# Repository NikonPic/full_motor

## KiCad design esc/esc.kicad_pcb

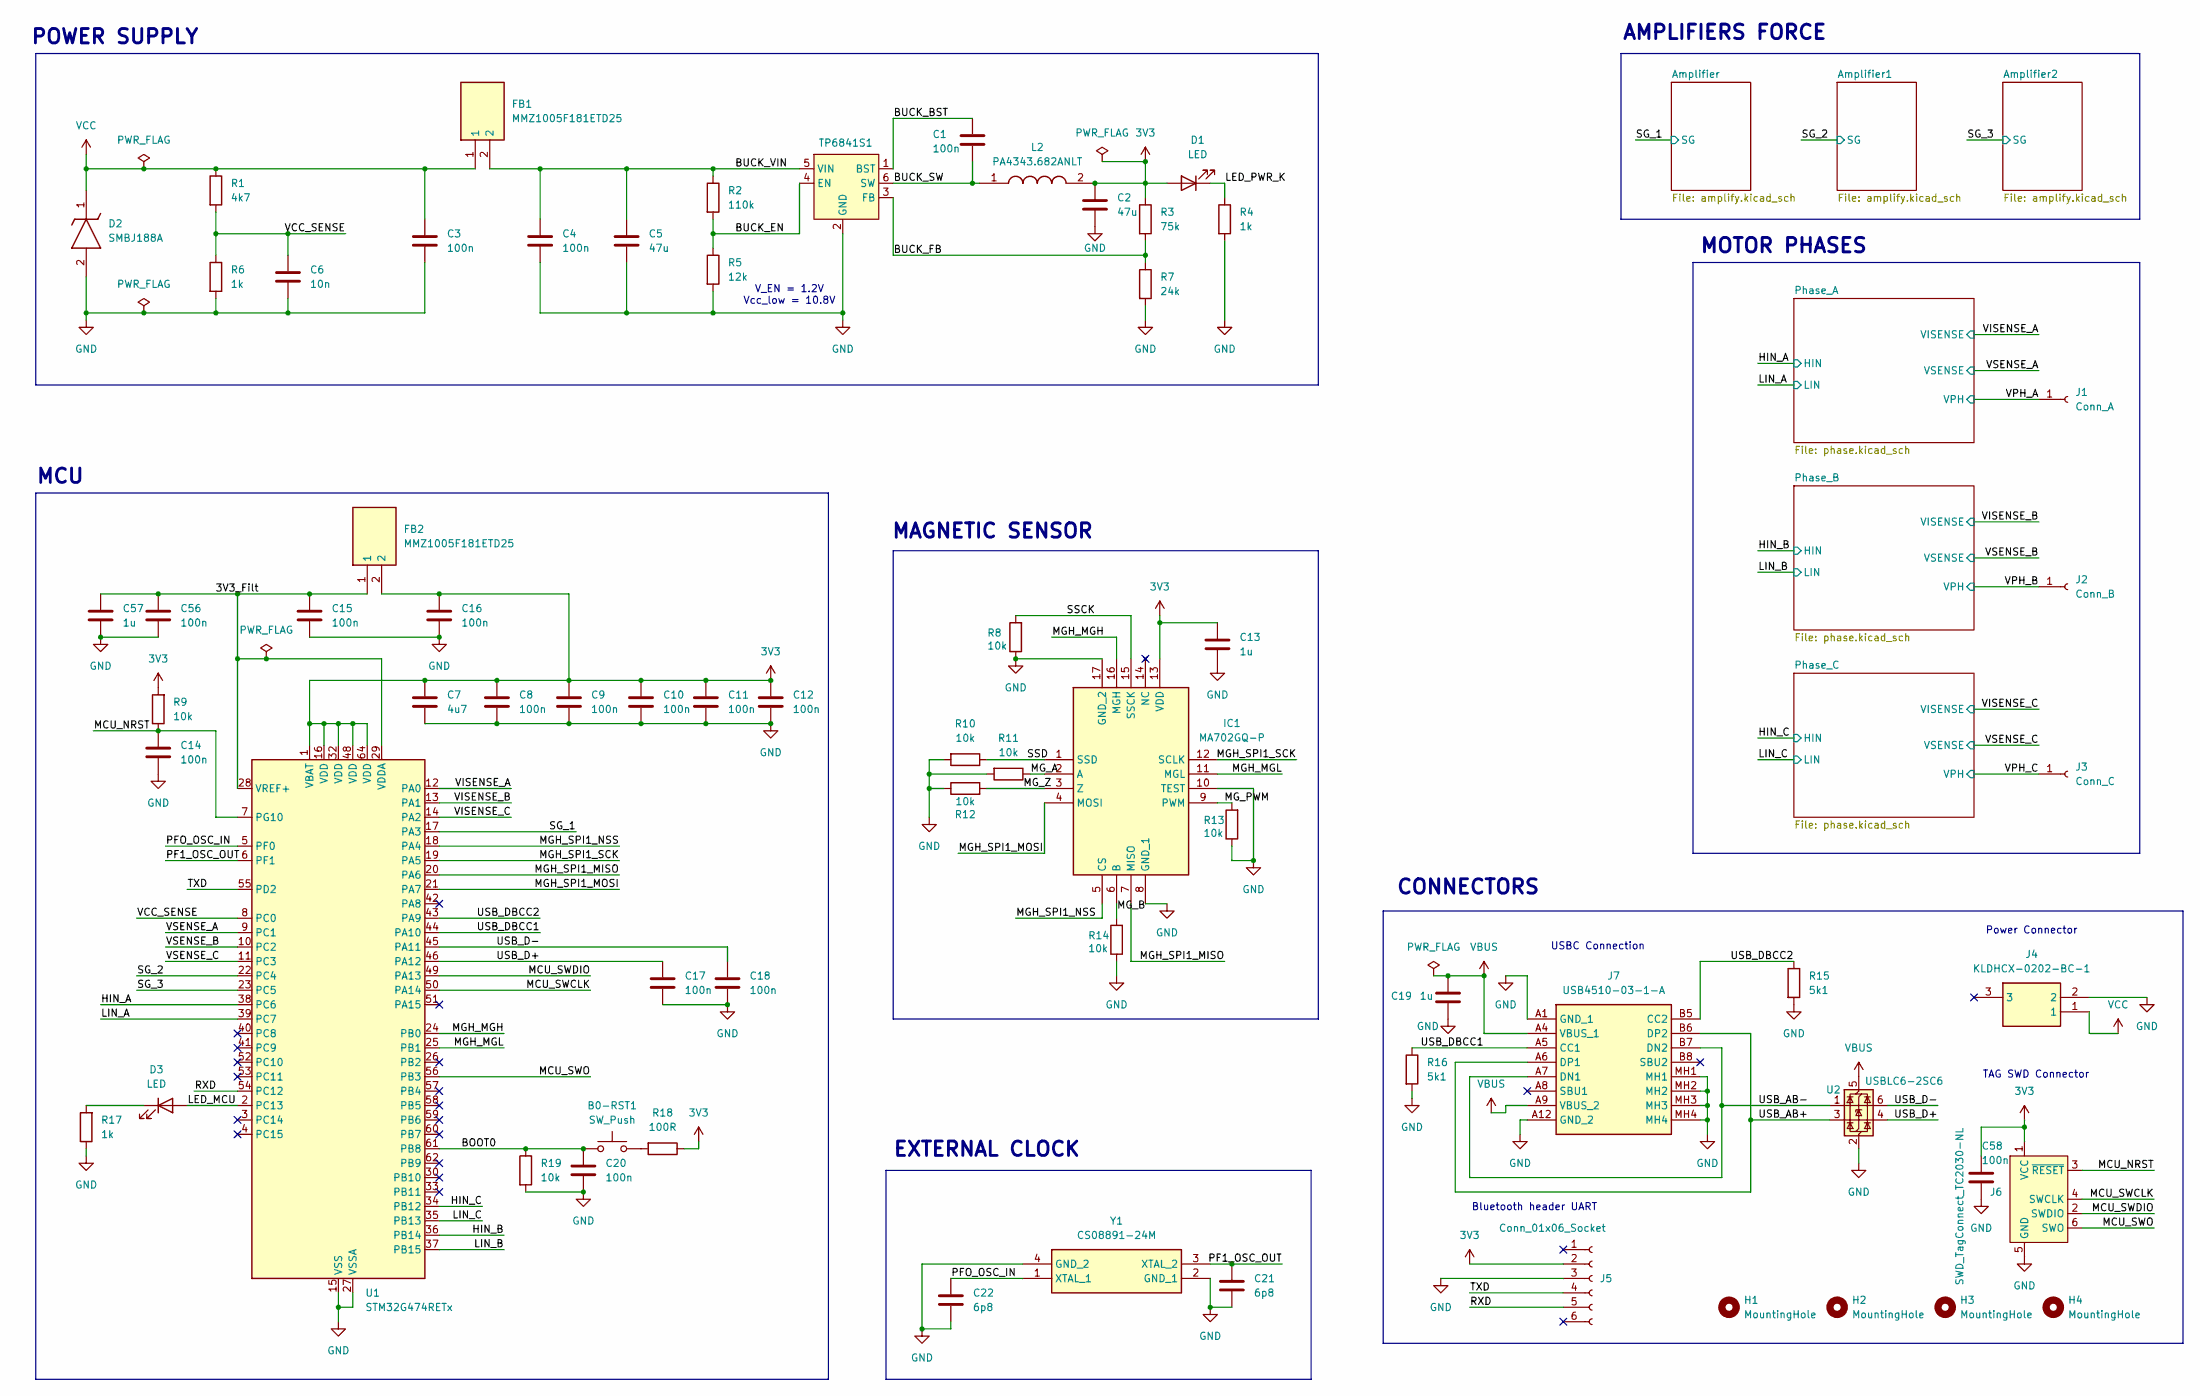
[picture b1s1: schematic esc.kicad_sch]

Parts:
B0-RST1: SW_Push; SW_SPST_B3U-1000P; MPN 653-B3U-1000P
C1, C3, C4, C8, C9, C10, C11, C12, C14, C15, C16, C17, C18, C20, C56, C58: 100n; C_0402_1005Metric; MPN 81-GRM02YR60G104ME1L
C2, C5: 47u; C_1206_3216Metric; Manufacturer_Part_Number MLASE31LBB5476MTNA01; Mouser Part Number 963-MLASE31LBB5476MT
C6: 10n; C_0402_1005Metric; MPN 77-V0402Y103KXJAC31X
C7: 4u7; C_0603_1608Metric; MPN 963-MLASE168AB5475KT
C13, C19, C57: 1u; C_0603_1608Metric; MPN 963-BJCT168CB7105KR
C21, C22: 6p8; C_0402_1005Metric; MPN 81-GJM0225C1C6R8CB1L
D1, D3: LED; LED_0603_1608Metric; MPN 720-GWJTLMS3.G3G758
D2: SMBJ188A; DIOM5436X244N; Manufacturer_Part_Number SMBJ18A
FB1, FB2: MMZ1005F181ETD25; BEADC1005X55N; Manufacturer_Part_Number MMZ1005F181ETD25; Mouser Part Number 810-MMZ1005F181ETD25
H1, H2, H3, H4: MountingHole; MountingHole_3.2mm_M3
IC1: MA702GQ-P; QFN50P300X300X100-17N-D; Manufacturer_Part_Number MA702GQ-P; Mouser Part Number 946-MA702GQ-P
J1: Conn_A; SolderWire-2sqmm_1x01_D2mm_OD3.9mm
J2: Conn_B; SolderWire-2sqmm_1x01_D2mm_OD3.9mm
J3: Conn_C; SolderWire-2sqmm_1x01_D2mm_OD3.9mm
J4: KLDHCX-0202-BC-1; KLDHCX0202BC1; Manufacturer_Part_Number KLDHCX-0202-BC-1; Mouser Part Number 806-KLDHCX-0202-BC-1
J5: Conn_01x06_Socket; PinSocket_1x06_P2.54mm_Vertical; MPN 437-3158710641003101
J6: SWD_TagConnect_TC2030-NL; Tag-Connect_TC2030-IDC-NL_2x03_P1.27mm_Vertical
J7: USB4510-03-1-A; USB4510031A; Manufacturer_Part_Number USB4510-03-1-A; Mouser Part Number 640-USB4510031A
L2: PA4343.682ANLT; INDPM135126X650N; Manufacturer_Part_Number PA4343.682ANLT; Mouser Part Number 673-PA4343.682ANLT
R1: 4k7; R_0603_1608Metric; MPN 754-RG1608N-472-WT5
R2: 110k; R_0603_1608Metric; MPN 594-MCT06030C1103FP5
R3: 75k; R_0603_1608Metric; MPN 603-RT0603FRE1375KL
R4, R6, R17: 1k; R_0603_1608Metric; MPN 71-CRCW06031K00FKED
R5: 12k; R_0603_1608Metric; MPN 594-MCS04020D1202BE0
R7: 24k; R_0603_1608Metric; MPN 667-ERA-3AEB243V
R8, R9, R10, R11, R12, R13, R14, R19: 10k; R_0603_1608Metric; MPN 708-RNCE0603BTE10K0
R15, R16: 5k1; R_0603_1608Metric; MPN 594-MCT06030C5101FPW
R18: 100R; R_0603_1608Metric; MPN 708-RNCE0603BTE100R
TP6841S1: SOT-23-6
U1: STM32G474RETx; LQFP-64_10x10mm_P0.5mm; MPN 511-STM32G474RET6
U2: USBLC6-2SC6; SOT-23-6; Manufacturer_Part_Number USBLC6-2SC6; Mouser Part Number 511-USBLC6-2SC6
Y1: CS08891-24M; NX2016SA24MEXS00ACS08891; Manufacturer_Part_Number NX2016SA-24M-EXS00A-CS08891; Mouser Part Number 344-NX2016SA24S08891

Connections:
3V3: C2.1, C7.1, C8.1, C9.1, C10.1, C11.1, C12.1, C13.1, C16.1, C58.1, D1.2 (A), FB2.2, IC1.13 (VDD), J5.2, J6.1 (VCC), L2.2, R3.1, R9.2, R18.1, U1.1 (VBAT), U1.16 (VDD), U1.32 (VDD), U1.48 (VDD), U1.64 (VDD); also elsewhere on the board
/3V3_Filt: C15.1, C56.1, C57.1, FB2.1, U1.28 (VREF+), U1.29 (VDDA)
/BOOT0: B0-RST1.1, C20.1, R19.1, U1.61 (PB8)
/BUCK_BST: C1.1, TP6841S1.1 (BST)
/BUCK_EN: R2.2, R5.1, TP6841S1.4 (EN)
/BUCK_FB: R3.2, R7.1, TP6841S1.3 (FB)
/BUCK_SW: C1.2, L2.1, TP6841S1.6 (SW)
/BUCK_VIN: C4.1, C5.1, FB1.2, R2.1, TP6841S1.5 (VIN)
/HIN_A: U1.38 (PC6); also elsewhere on the board
/HIN_B: U1.36 (PB14); also elsewhere on the board
/HIN_C: U1.34 (PB12); also elsewhere on the board
/LED_MCU: D3.2 (A), U1.2 (PC13)
/LED_PWR_K: D1.1 (K), R4.1
/LIN_A: U1.39 (PC7); also elsewhere on the board
/LIN_B: U1.37 (PB15); also elsewhere on the board
/LIN_C: U1.35 (PB13); also elsewhere on the board
/MCU_NRST: C14.1, J6.3 (~RESET), R9.1, U1.7 (PG10)
/MCU_SWCLK: J6.4 (SWCLK), U1.50 (PA14)
/MCU_SWDIO: J6.2 (SWDIO), U1.49 (PA13)
/MCU_SWO: J6.6 (SWO), U1.56 (PB3)
/MGH_MGH: IC1.16 (MGH), U1.24 (PB0)
/MGH_MGL: IC1.11 (MGL), U1.25 (PB1)
/MGH_SPI1_MISO: IC1.7 (MISO), U1.20 (PA6)
/MGH_SPI1_MOSI: IC1.4 (MOSI), U1.21 (PA7)
/MGH_SPI1_NSS: IC1.5 (CS), U1.18 (PA4)
/MGH_SPI1_SCK: IC1.12 (SCLK), U1.19 (PA5)
/MG_A: IC1.2 (A), R11.1
/MG_B: IC1.6 (B), R14.2
/MG_PWM: IC1.9 (PWM), R13.2
/MG_Z: IC1.3 (Z), R12.2
/PF1_OSC_OUT: C21.1, U1.6 (PF1), Y1.3 (XTAL_2)
/PFO_OSC_IN: C22.1, U1.5 (PF0), Y1.1 (XTAL_1)
/RXD: J5.5, U1.54 (PC12)
/SG_1: U1.17 (PA3); also elsewhere on the board
/SG_2: U1.22 (PC4); also elsewhere on the board
/SG_3: U1.23 (PC5); also elsewhere on the board
/SSCK: IC1.15 (SSCK), R8.2
/SSD: IC1.1 (SSD), R10.1
/TXD: J5.4, U1.55 (PD2)
/USB_AB+: J7.A6 (DP1), J7.B6 (DP2), U2.3 (I/O2)
/USB_AB-: J7.A7 (DN1), J7.B7 (DN2), U2.1 (I/O1)
/USB_D+: C17.1, U1.46 (PA12), U2.4 (I/O2)
/USB_D-: C18.1, U1.45 (PA11), U2.6 (I/O1)
/USB_DBCC1: J7.A5 (CC1), R16.1, U1.44 (PA10)
/USB_DBCC2: J7.B5 (CC2), R15.1, U1.43 (PA9)
/VCC_SENSE: C6.1, R1.2, R6.1, U1.8 (PC0)
/VISENSE_A: U1.12 (PA0); also elsewhere on the board
/VISENSE_B: U1.13 (PA1); also elsewhere on the board
/VISENSE_C: U1.14 (PA2); also elsewhere on the board
/VPH_A: J1.1; also elsewhere on the board
/VPH_B: J2.1; also elsewhere on the board
/VPH_C: J3.1; also elsewhere on the board
/VSENSE_A: U1.9 (PC1); also elsewhere on the board
/VSENSE_B: U1.10 (PC2); also elsewhere on the board
/VSENSE_C: U1.11 (PC3); also elsewhere on the board
GND: C2.2, C3.2, C4.2, C5.2, C6.2, C7.2, C8.2, C9.2, C10.2, C11.2, C12.2, C13.2, C14.2, C15.2, C16.2, C17.2, C18.2, C19.2, C20.2, C21.2, C22.2, C56.2, C57.2, C58.2, D2.2 (A), IC1.8 (GND_1), IC1.10 (TEST), IC1.17 (GND_2), J4.2, J5.3, J6.5 (GND), J7.A1 (GND_1), J7.A12 (GND_2), J7.MH1, J7.MH2, J7.MH3, J7.MH4, R4.2, R5.2, R6.2, R7.2, R8.1, R10.2, R11.2, R12.1, R13.1, R14.1, R15.2, R16.2, R17.1, R19.2, TP6841S1.2 (GND), U1.15 (VSS), U1.27 (VSSA), U1.31 (VSS), U1.47 (VSS), U1.63 (VSS), U2.2 (GND), Y1.2 (GND_1), Y1.4 (GND_2); also elsewhere on the board
unnamed: B0-RST1.2, R18.2
unnamed: D3.1 (K), R17.2
VBUS: C19.1, J7.A4 (VBUS_1), J7.A9 (VBUS_2), U2.5 (VBUS)
VCC: C3.1, D2.1 (K), FB1.1, J4.1, R1.1; also elsewhere on the board

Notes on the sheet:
MOTOR PHASES
POWER SUPPLY
CONNECTORS
MCU
TAG SWD Connector
Power Connector
AMPLIFIERS FORCE
USBC Connection
MAGNETIC SENSOR
V_EN = 1.2V Vcc_low = 10.8V
EXTERNAL CLOCK
Bluetooth header UART

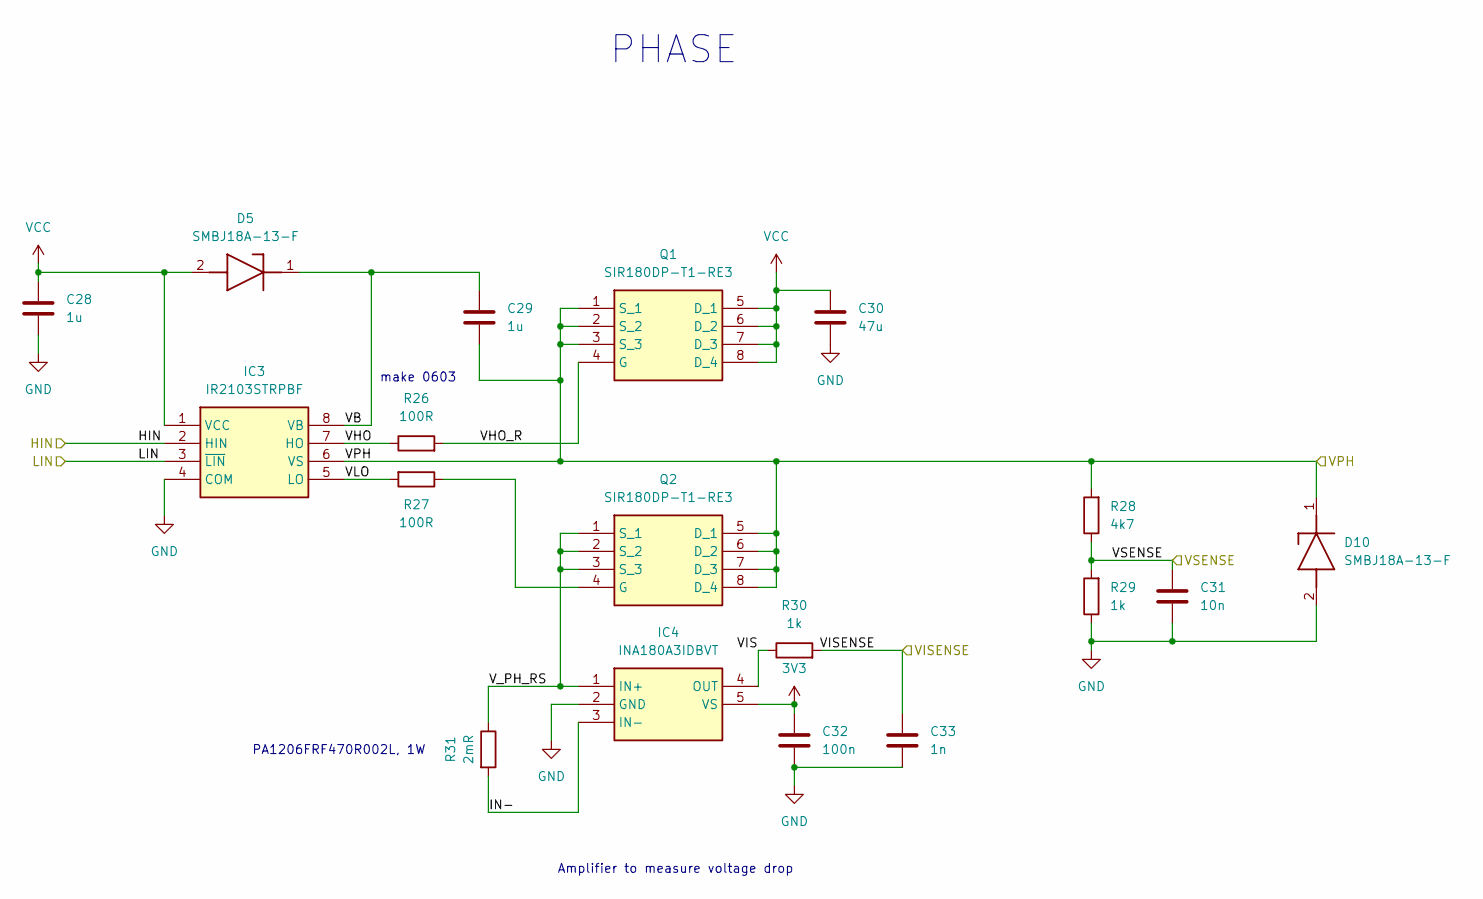
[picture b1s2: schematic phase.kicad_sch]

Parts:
C28, C29: 1u; C_0603_1608Metric; MPN 963-BJCT168CB7105KR
C30: 47u; C_1206_3216Metric; Manufacturer_Part_Number MLASE31LBB5476MTNA01; Mouser Part Number 963-MLASE31LBB5476MT
C31: 10n; C_0402_1005Metric; MPN 77-V0402Y103KXJAC31X
C32: 100n; C_0402_1005Metric; MPN 81-GRM02YR60G104ME1L
C33: 1n; C_0402_1005Metric; MPN 963-MLASE042SB5102MW
D5, D10: SMBJ18A-13-F; DIOM5336X250N; Manufacturer_Part_Number SMBJ18A-13-F; Mouser Part Number 621-SMBJ18A-13-F
IC3: IR2103STRPBF; SOIC127P600X175-8N; Manufacturer_Part_Number IR2103STRPBF; Mouser Part Number 942-IR2103STRPBF
IC4: INA180A3IDBVT; SOT95P280X145-5N; Manufacturer_Part_Number INA180A3IDBVT; Mouser Part Number 595-INA180A3IDBVT
Q1, Q2: SIR180DP-T1-RE3; SI7141DPT1GE3; Manufacturer_Part_Number SiR180DP-T1-RE3; Mouser Part Number 78-SIR180DP-T1-RE3
R26, R27: 100R; R_0603_1608Metric; MPN 708-RNCE0603BTE100R
R28: 4k7; R_0603_1608Metric; MPN 754-RG1608N-472-WT5
R29, R30: 1k; R_0603_1608Metric; MPN 71-CRCW06031K00FKED
R31: 2mR; R_1206_3216Metric; MPN 603-P1206FRF470R002L

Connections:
3V3: C32.1, IC4.5 (VS); also elsewhere on the board
/HIN_A: IC3.2 (HIN); also elsewhere on the board
/LIN_A: IC3.3 (~LIN); also elsewhere on the board
/Phase_A/IN-: IC4.3 (IN-), R31.2
/Phase_A/VB: C29.1, D5.1 (K), IC3.8 (VB)
/Phase_A/VHO: IC3.7 (HO), R26.1
/Phase_A/VHO_R: Q1.4 (G), R26.2
/Phase_A/VIS: IC4.4 (OUT), R30.1
/Phase_A/VLO: IC3.5 (LO), R27.2
/Phase_A/V_PH_RS: IC4.1 (IN+), Q2.1 (S_1), Q2.2 (S_2), Q2.3 (S_3), R31.1
/VISENSE_A: C33.1, R30.2; also elsewhere on the board
/VPH_A: C29.2, D10.1 (K), IC3.6 (VS), Q1.1 (S_1), Q1.2 (S_2), Q1.3 (S_3), Q2.5 (D_1), Q2.6 (D_2), Q2.7 (D_3), Q2.8 (D_4), R28.2; also elsewhere on the board
/VSENSE_A: C31.1, R28.1, R29.2; also elsewhere on the board
GND: C28.2, C30.2, C31.2, C32.2, C33.2, D10.2 (A), IC3.4 (COM), IC4.2 (GND), R29.1; also elsewhere on the board
unnamed: Q2.4 (G), R27.1
VCC: C28.1, C30.1, D5.2 (A), IC3.1 (VCC), Q1.5 (D_1), Q1.6 (D_2), Q1.7 (D_3), Q1.8 (D_4); also elsewhere on the board

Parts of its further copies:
C34, C35, C45, C46: 1u; C_0603_1608Metric; MPN 963-BJCT168CB7105KR
C36, C47: 47u; C_1206_3216Metric; Manufacturer_Part_Number MLASE31LBB5476MTNA01; Mouser Part Number 963-MLASE31LBB5476MT
C37, C48: 10n; C_0402_1005Metric; MPN 77-V0402Y103KXJAC31X
C38, C49: 100n; C_0402_1005Metric; MPN 81-GRM02YR60G104ME1L
C39, C50: 1n; C_0402_1005Metric; MPN 963-MLASE042SB5102MW
D7, D9, D11, D12: SMBJ18A-13-F; DIOM5336X250N; Manufacturer_Part_Number SMBJ18A-13-F; Mouser Part Number 621-SMBJ18A-13-F
IC5, IC8: IR2103STRPBF; SOIC127P600X175-8N; Manufacturer_Part_Number IR2103STRPBF; Mouser Part Number 942-IR2103STRPBF
IC6, IC9: INA180A3IDBVT; SOT95P280X145-5N; Manufacturer_Part_Number INA180A3IDBVT; Mouser Part Number 595-INA180A3IDBVT
Q3, Q4, Q5, Q6: SIR180DP-T1-RE3; SI7141DPT1GE3; Manufacturer_Part_Number SiR180DP-T1-RE3; Mouser Part Number 78-SIR180DP-T1-RE3
R32, R33, R44, R45: 100R; R_0603_1608Metric; MPN 708-RNCE0603BTE100R
R34, R46: 4k7; R_0603_1608Metric; MPN 754-RG1608N-472-WT5
R35, R36, R47, R48: 1k; R_0603_1608Metric; MPN 71-CRCW06031K00FKED
R37, R49: 2mR; R_1206_3216Metric; MPN 603-P1206FRF470R002L

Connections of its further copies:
3V3: C38.1, C49.1, IC6.5 (VS), IC9.5 (VS); also elsewhere on the board
/HIN_B: IC5.2 (HIN); also elsewhere on the board
/HIN_C: IC8.2 (HIN); also elsewhere on the board
/LIN_B: IC5.3 (~LIN); also elsewhere on the board
/LIN_C: IC8.3 (~LIN); also elsewhere on the board
/Phase_B/IN-: IC6.3 (IN-), R37.2
/Phase_B/VB: C35.1, D7.1 (K), IC5.8 (VB)
/Phase_B/VHO: IC5.7 (HO), R32.1
/Phase_B/VHO_R: Q3.4 (G), R32.2
/Phase_B/VIS: IC6.4 (OUT), R36.1
/Phase_B/VLO: IC5.5 (LO), R33.2
/Phase_B/V_PH_RS: IC6.1 (IN+), Q4.1 (S_1), Q4.2 (S_2), Q4.3 (S_3), R37.1
/Phase_C/IN-: IC9.3 (IN-), R49.2
/Phase_C/VB: C46.1, D9.1 (K), IC8.8 (VB)
/Phase_C/VHO: IC8.7 (HO), R44.1
/Phase_C/VHO_R: Q5.4 (G), R44.2
/Phase_C/VIS: IC9.4 (OUT), R48.1
/Phase_C/VLO: IC8.5 (LO), R45.2
/Phase_C/V_PH_RS: IC9.1 (IN+), Q6.1 (S_1), Q6.2 (S_2), Q6.3 (S_3), R49.1
/VISENSE_B: C39.1, R36.2; also elsewhere on the board
/VISENSE_C: C50.1, R48.2; also elsewhere on the board
/VPH_B: C35.2, D11.1 (K), IC5.6 (VS), Q3.1 (S_1), Q3.2 (S_2), Q3.3 (S_3), Q4.5 (D_1), Q4.6 (D_2), Q4.7 (D_3), Q4.8 (D_4), R34.2; also elsewhere on the board
/VPH_C: C46.2, D12.1 (K), IC8.6 (VS), Q5.1 (S_1), Q5.2 (S_2), Q5.3 (S_3), Q6.5 (D_1), Q6.6 (D_2), Q6.7 (D_3), Q6.8 (D_4), R46.2; also elsewhere on the board
/VSENSE_B: C37.1, R34.1, R35.2; also elsewhere on the board
/VSENSE_C: C48.1, R46.1, R47.2; also elsewhere on the board
GND: C34.2, C36.2, C37.2, C38.2, C39.2, C45.2, C47.2, C48.2, C49.2, C50.2, D11.2 (A), D12.2 (A), IC5.4 (COM), IC6.2 (GND), IC8.4 (COM), IC9.2 (GND), R35.1, R47.1; also elsewhere on the board
unnamed: Q4.4 (G), R33.1
unnamed: Q6.4 (G), R45.1
VCC: C34.1, C36.1, C45.1, C47.1, D7.2 (A), D9.2 (A), IC5.1 (VCC), IC8.1 (VCC), Q3.5 (D_1), Q3.6 (D_2), Q3.7 (D_3), Q3.8 (D_4), Q5.5 (D_1), Q5.6 (D_2), Q5.7 (D_3), Q5.8 (D_4); also elsewhere on the board

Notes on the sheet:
PA1206FRF470R002L, 1W
PHASE
make 0603
Amplifier to measure voltage drop

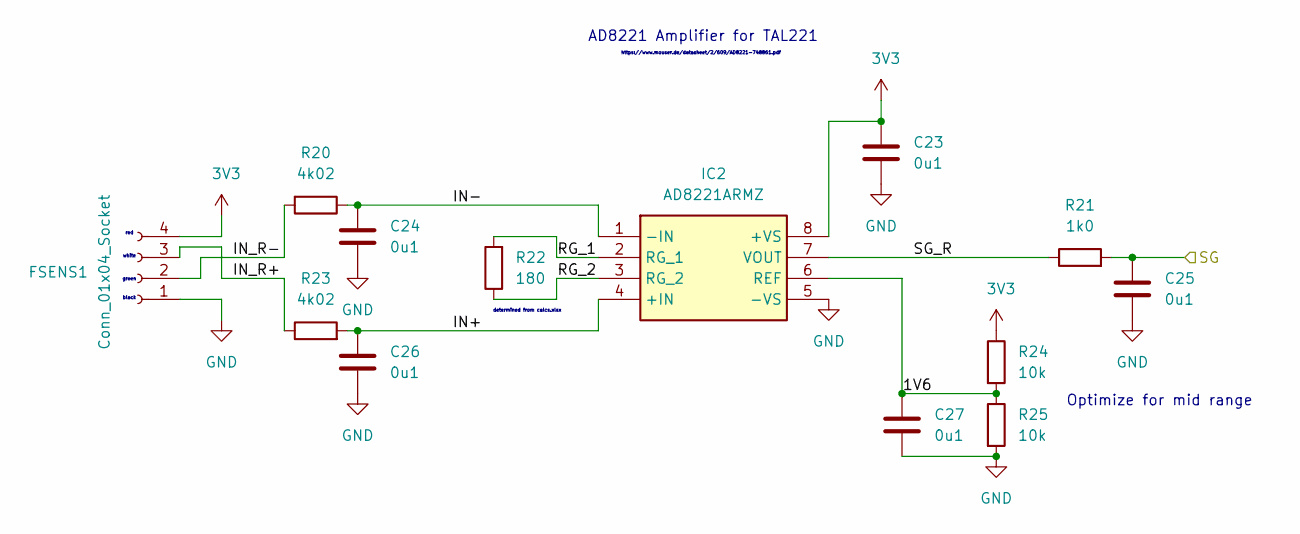
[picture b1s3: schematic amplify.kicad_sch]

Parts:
C23, C24, C25, C26, C27: 0u1; C_0603_1608Metric; MPN 187-CL10B104KB8NFNC
FSENS1: Conn_01x04_Socket; JST_XH_S4B-XH-A-1_1x04_P2.50mm_Horizontal; MPN 306-S4B-XH-ALFSN
IC2: AD8221ARMZ; SOP65P490X110-8N; Manufacturer_Part_Number AD8221ARMZ; Mouser Part Number 584-AD8221ARMZ
R20, R23: 4k02; R_0603_1608Metric; MPN 754-RR0816P-4021D59H
R21: 1k0; R_0603_1608Metric; MPN 71-CRCW06031K00FKED
R22: 180; R_0603_1608Metric; MPN 603-RT0603FRD07180RL
R24, R25: 10k; R_0603_1608Metric; MPN 708-RNCE0603BTE10K0

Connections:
3V3: C23.1, FSENS1.4, IC2.8 (+VS), R24.1; also elsewhere on the board
/Amplifier1/1V6: C27.1, IC2.6 (REF), R24.2, R25.1
/Amplifier1/IN+: C26.1, IC2.4 (+IN), R23.2
/Amplifier1/IN-: C24.1, IC2.1 (-IN), R20.1
/Amplifier1/IN_R+: FSENS1.3, R23.1
/Amplifier1/IN_R-: FSENS1.2, R20.2
/Amplifier1/RG_1: IC2.2 (RG_1), R22.2
/Amplifier1/RG_2: IC2.3 (RG_2), R22.1
/Amplifier1/SG_R: IC2.7 (VOUT), R21.1
/SG_2: C25.1, R21.2; also elsewhere on the board
GND: C23.2, C24.2, C25.2, C26.2, C27.2, FSENS1.1, IC2.5 (-VS), R25.2; also elsewhere on the board

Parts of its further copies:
C40, C41, C42, C43, C44, C51, C52, C53, C54, C55: 0u1; C_0603_1608Metric; MPN 187-CL10B104KB8NFNC
FSENS2, FSENS3: Conn_01x04_Socket; JST_XH_S4B-XH-A-1_1x04_P2.50mm_Horizontal; MPN 306-S4B-XH-ALFSN
IC7, IC10: AD8221ARMZ; SOP65P490X110-8N; Manufacturer_Part_Number AD8221ARMZ; Mouser Part Number 584-AD8221ARMZ
R38, R41, R50, R53: 4k02; R_0603_1608Metric; MPN 754-RR0816P-4021D59H
R39, R51: 1k0; R_0603_1608Metric; MPN 71-CRCW06031K00FKED
R40, R52: 180; R_0603_1608Metric; MPN 603-RT0603FRD07180RL
R42, R43, R54, R55: 10k; R_0603_1608Metric; MPN 708-RNCE0603BTE10K0

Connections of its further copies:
3V3: C40.1, C51.1, FSENS2.4, FSENS3.4, IC7.8 (+VS), IC10.8 (+VS), R42.1, R54.1; also elsewhere on the board
/Amplifier2/1V6: C55.1, IC10.6 (REF), R54.2, R55.1
/Amplifier2/IN+: C54.1, IC10.4 (+IN), R53.2
/Amplifier2/IN-: C52.1, IC10.1 (-IN), R50.1
/Amplifier2/IN_R+: FSENS3.3, R53.1
/Amplifier2/IN_R-: FSENS3.2, R50.2
/Amplifier2/RG_1: IC10.2 (RG_1), R52.2
/Amplifier2/RG_2: IC10.3 (RG_2), R52.1
/Amplifier2/SG_R: IC10.7 (VOUT), R51.1
/Amplifier/1V6: C44.1, IC7.6 (REF), R42.2, R43.1
/Amplifier/IN+: C43.1, IC7.4 (+IN), R41.2
/Amplifier/IN-: C41.1, IC7.1 (-IN), R38.1
/Amplifier/IN_R+: FSENS2.3, R41.1
/Amplifier/IN_R-: FSENS2.2, R38.2
/Amplifier/RG_1: IC7.2 (RG_1), R40.2
/Amplifier/RG_2: IC7.3 (RG_2), R40.1
/Amplifier/SG_R: IC7.7 (VOUT), R39.1
/SG_1: C42.1, R39.2; also elsewhere on the board
/SG_3: C53.1, R51.2; also elsewhere on the board
GND: C40.2, C41.2, C42.2, C43.2, C44.2, C51.2, C52.2, C53.2, C54.2, C55.2, FSENS2.1, FSENS3.1, IC7.5 (-VS), IC10.5 (-VS), R43.2, R55.2; also elsewhere on the board

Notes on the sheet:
Optimize for mid range
https://www.mouser.de/datasheet/2/609/AD8221-748861.pdf
red
green
white
AD8221 Amplifier for TAL221
black
determined from calcs.xlsx

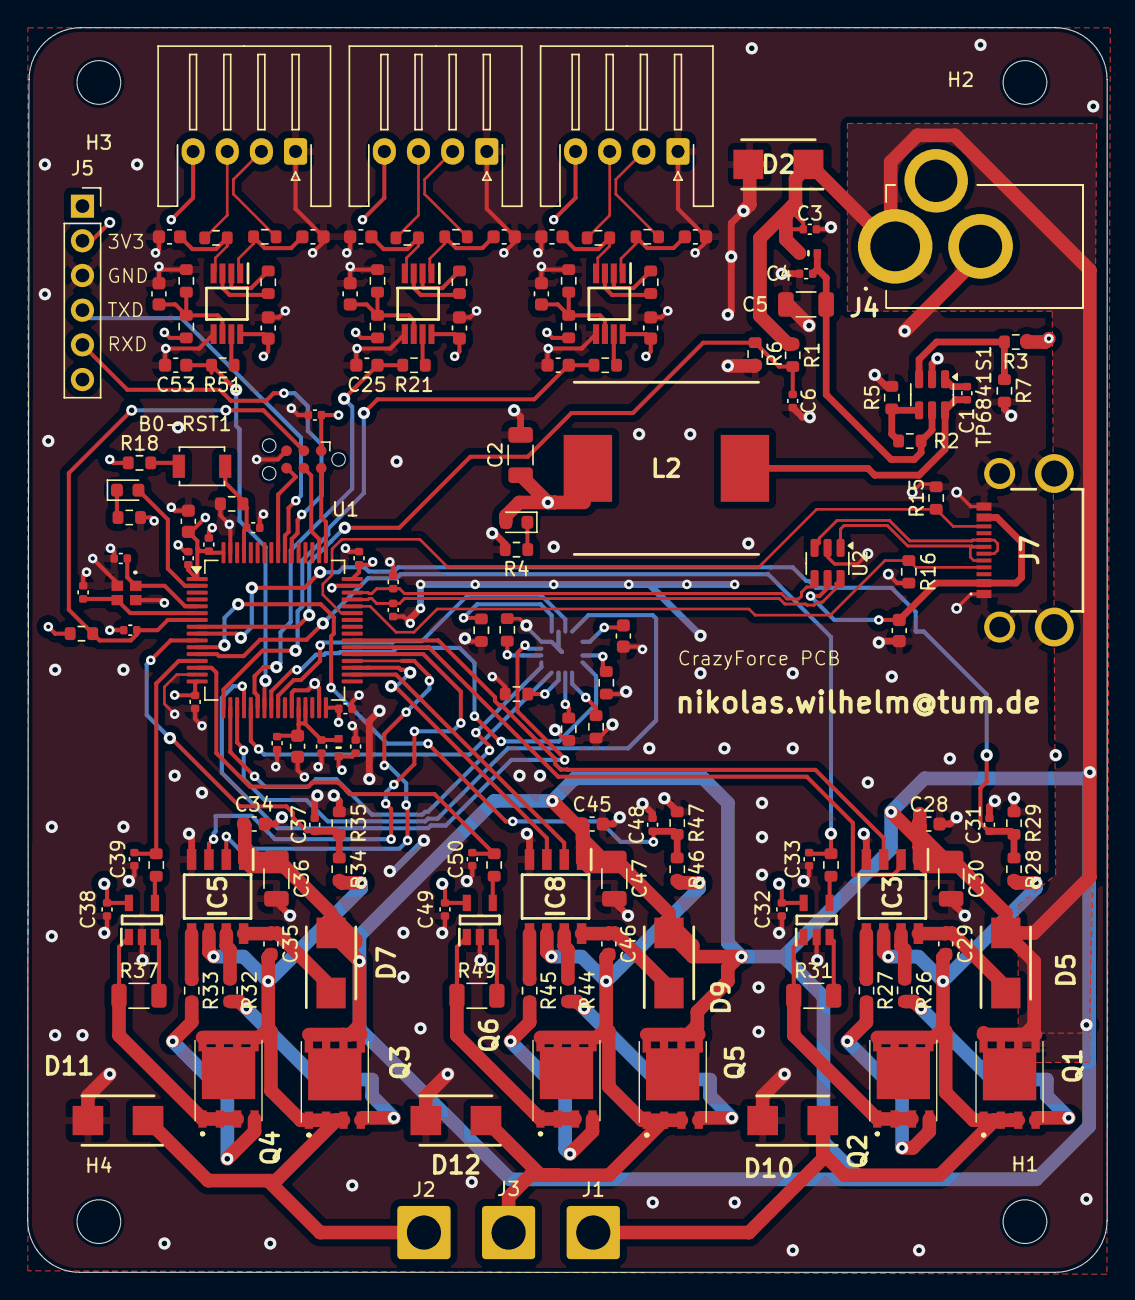
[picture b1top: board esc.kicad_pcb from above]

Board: 4 copper layers, 79.0 x 91.1 mm, 160 parts (1 on the bottom side), 108 nets.

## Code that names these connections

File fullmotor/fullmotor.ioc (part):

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Mcu.Name=STM32G474R(B-C-E)Tx
Mcu.Package=LQFP64
Mcu.UserName=STM32G474RETx
PA0.Signal=ADC1_IN1
PA1.Signal=ADC2_IN2
PA10.Signal=UCPD1_DBCC2
PA11.Mode=Device
PA11.Signal=USB_DM
PA12.Mode=Device
PA12.Signal=USB_DP
PA13.Mode=Trace_Asynchronous_SW
PA13.Signal=SYS_JTMS-SWDIO
PA14.Mode=Trace_Asynchronous_SW
PA14.Signal=SYS_JTCK-SWCLK
PA2.Mode=IN3-Differential
PA2.Signal=ADC1_IN3
PA3.Mode=IN3-Differential
PA3.Signal=ADC1_IN4
PA4.Mode=NSS_Signal_Hard_Input
PA4.Signal=SPI1_NSS
PA5.Mode=Full_Duplex_Master
PA5.Signal=SPI1_SCK
PA6.Mode=Full_Duplex_Master
PA6.Signal=SPI1_MISO
PA7.Mode=Full_Duplex_Master
PA7.Signal=SPI1_MOSI
PA9.Signal=UCPD1_DBCC1
PB0.Signal=GPIO_Input
PB1.Signal=GPIO_Input
PB12.Mode=Output_TC1TC2
PB12.Signal=HRTIM1_CHC1
PB13.Mode=Output_TC1TC2
PB13.Signal=HRTIM1_CHC2
PB14.Mode=Output_TD1TD2
PB14.Signal=HRTIM1_CHD1
PB15.Mode=Output_TD1TD2
PB15.Signal=HRTIM1_CHD2
PB3.Mode=Trace_Asynchronous_SW
PB3.Signal=SYS_JTDO-SWO
PC0.Signal=ADC1_IN6
PC1.Signal=ADC2_IN7
PC12.Mode=Asynchronous
PC12.Signal=UART5_TX
PC2.Signal=ADC1_IN8
PC3.Signal=ADC2_IN9
PC4.Signal=ADC2_IN5
PC5.Signal=ADC2_IN11
PC6.Mode=Output_TF1TF2
PC6.Signal=HRTIM1_CHF1
PC7.Mode=Output_TF1TF2
PC7.Signal=HRTIM1_CHF2
PD2.Mode=Asynchronous
PD2.Signal=UART5_RX
RCC.HSE_VALUE=8000000
RCC.SYSCLKFreq_VALUE=16000000
board=custom

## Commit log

2025-04-29 init commit esc design
2025-05-05 with phase
2025-05-13 esc changes
2025-05-30 full layout
2025-06-02 ready for production..?
2025-09-02 adding esc kicad and stm32cubeide project
2025-09-05 with the used libraries
